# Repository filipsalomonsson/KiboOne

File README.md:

# Kibo One

A keyboard built from the ground up to my personal preferences, using switches and keycaps from 1980s Apple keyboards. Very much a work in progress.

Some design guidelines:

* Must be fun to make
* Alps switches are nice
* AEK-era Apple keycaps are nice
* Stabilizers are the devil
* The width of standard ANSI shift keys is ridiculous
* The width of a standard spacebar is ridiculous
* Actually, no key _really_ deserves to be wider than 2u
* The thumb is underused for modifier keys
* The left-leaning stagger for the left hand on standard keyboards seems a bit silly

More to come.

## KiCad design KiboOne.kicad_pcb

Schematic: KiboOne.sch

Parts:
C1, C2: 22pF; C_0805_2012Metric_Pad1.15x1.40mm_HandSolder
C3, C4: 1uF; C_0805_2012Metric_Pad1.15x1.40mm_HandSolder
D1, D2, D3, D4, D5, D6, D7, D8, D9, D10, D11, D12, D13, D14, D15, D16, D17, D18, D19, D20, D21, D22, D23, D24, D25, D26, D27, D28, D29, D30, D31, D32, D33, D34, D35, D36, D37, D38, D39, D40, D41, D42, D43, D44, D45, D46, D47, D48, D49, D50, D51, D52, D53, D54, D55, D56, D57, D58, D59, D60, D61, D62, D63: LL4148; D_MiniMELF
J1: USB_C_Receptacle; USB_C_Receptacle_Amphenol_12401548E4-2A
R1, R2, R3: 22ohm; R_0805_2012Metric_Pad1.15x1.40mm_HandSolder
SW1: \\; SW_Matias_1.00u
SW2: =; SW_Matias_1.00u
SW3: -; SW_Matias_1.00u
SW4: 0; SW_Matias_1.00u
SW5: 9; SW_Matias_1.00u
SW6: 8; SW_Matias_1.00u
SW7: 7; SW_Matias_1.00u
SW8: 6; SW_Matias_1.00u
SW9: 5; SW_Matias_1.00u
SW10: 4; SW_Matias_1.00u
SW11: 3; SW_Matias_1.00u
SW12: 2; SW_Matias_1.00u
SW13: 1; SW_Matias_1.00u
SW14: esc; SW_Matias_1.00u
SW15: del; SW_Matias_1.50u
SW16: ]; SW_Matias_1.00u
SW17: [; SW_Matias_1.00u
SW18: P; SW_Matias_1.00u
SW19: O; SW_Matias_1.00u
SW20: I; SW_Matias_1.00u
SW21: U; SW_Matias_1.00u
SW22: Y; SW_Matias_1.00u
SW23: T; SW_Matias_1.00u
SW24: R; SW_Matias_1.00u
SW25: E; SW_Matias_1.00u
SW26: W; SW_Matias_1.00u
SW27: Q; SW_Matias_1.00u
SW28: ⇥; SW_Matias_1.50u
SW29: return; SW_Matias_2.00u
SW30: '; SW_Matias_1.00u
SW31: ;; SW_Matias_1.00u
SW32: L; SW_Matias_1.00u
SW33: K; SW_Matias_1.00u
SW34: J; SW_Matias_1.00u
SW35: H; SW_Matias_1.00u
SW36: G; SW_Matias_1.00u
SW37: F; SW_Matias_1.00u
SW38: D; SW_Matias_1.00u
SW39: S; SW_Matias_1.00u
SW40: A; SW_Matias_1.00u
SW41: cmd1; SW_Matias_1.50u
SW42: /; SW_Matias_1.00u
SW43: ↑; SW_Matias_1.00u
SW44: .; SW_Matias_1.00u
SW45: ,; SW_Matias_1.00u
SW46: M; SW_Matias_1.00u
SW47: N; SW_Matias_1.00u
SW48: B; SW_Matias_1.00u
SW49: V; SW_Matias_1.00u
SW50: C; SW_Matias_1.00u
SW51: X; SW_Matias_1.00u
SW52: Z; SW_Matias_1.00u
SW53: tilde; SW_Matias_1.00u
SW54: shift; SW_Matias_1.50u
SW55: →; SW_Matias_1.00u
SW56: ↓; SW_Matias_1.00u
SW57: ←; SW_Matias_1.00u
SW58: cmd3; SW_Matias_1.50u
SW59: space; SW_Matias_2.25u
SW60: Fn; SW_Matias_1.00u
SW61: cmd2; SW_Matias_1.75u
SW62: ⌥; SW_Matias_1.25u
SW63: ctrl; SW_Matias_1.50u
SW_RESET1: RESET; SW_SPST_EVPBF
U1: ATmega32U4-AU; TQFP-44_10x10mm_P0.8mm
Y1: 16 MHz; Crystal_SMD_3225-4Pin_3.2x2.5mm_HandSoldering

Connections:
/D1+: J1.A6, J1.B6, R2.2
/D1-: J1.A7, J1.B7, R1.2
Col1: D8.1, D9.1, D22.1, D23.1, D35.1, D36.1, D48.1, D49.1, U1.18 (PD0)
Col2: D7.1, D10.1, D21.1, D24.1, D34.1, D37.1, D47.1, D50.1, U1.28 (PB4)
Col3: D6.1, D11.1, D20.1, D25.1, D33.1, D38.1, D46.1, D51.1, U1.19 (PD1)
Col4: D5.1, D12.1, D19.1, D26.1, D32.1, D39.1, D45.1, D52.1, U1.27 (PD7)
Col5: D4.1, D13.1, D18.1, D27.1, D31.1, D40.1, D44.1, D53.1, U1.20 (PD2)
Col6: D3.1, D14.1, D17.1, D28.1, D30.1, D41.1, D54.1, D58.1, U1.26 (PD6)
Col7: D2.1, D16.1, D29.1, D59.1, D60.1, D61.1, D62.1, D63.1, U1.21 (PD3)
Col8: D1.1, D15.1, D42.1, D43.1, D55.1, D56.1, D57.1, U1.25 (PD4)
D+: R2.1, U1.4 (D+)
D-: R1.1, U1.3 (D-)
GND: C1.2, C2.2, C3.1, C4.2, J1.A1, J1.A12, J1.B1, J1.B12, J1.S1, SW_RESET1.2, U1.5 (UGND), U1.15 (GND), U1.23 (GND), U1.35 (GND), U1.43 (GND)
unnamed: C1.1, U1.17 (XTAL1), Y1.1
unnamed: C2.1, U1.16 (XTAL2), Y1.2
unnamed: C4.1, U1.6 (UCAP)
unnamed: D1.2, SW1.2
unnamed: D2.2, SW2.2
unnamed: D3.2, SW3.2
unnamed: D4.2, SW4.2
unnamed: D5.2, SW5.2
unnamed: D6.2, SW6.2
unnamed: D7.2, SW7.2
unnamed: D8.2, SW8.2
unnamed: D9.2, SW9.2
unnamed: D10.2, SW10.2
unnamed: D11.2, SW11.2
unnamed: D12.2, SW12.2
unnamed: D13.2, SW13.2
unnamed: D14.2, SW14.2
unnamed: D15.2, SW15.2
unnamed: D16.2, SW16.2
unnamed: D17.2, SW17.2
unnamed: D18.2, SW18.2
unnamed: D19.2, SW19.2
unnamed: D20.2, SW20.2
unnamed: D21.2, SW21.2
unnamed: D22.2, SW22.2
unnamed: D23.2, SW23.2
unnamed: D24.2, SW24.2
unnamed: D25.2, SW25.2
unnamed: D26.2, SW26.2
unnamed: D27.2, SW27.2
unnamed: D28.2, SW28.2
unnamed: D29.2, SW29.2
unnamed: D30.2, SW30.2
unnamed: D31.2, SW31.2
unnamed: D32.2, SW32.2
unnamed: D33.2, SW33.2
unnamed: D34.2, SW34.2
unnamed: D35.2, SW35.2
unnamed: D36.2, SW36.2
unnamed: D37.2, SW37.2
unnamed: D38.2, SW38.2
unnamed: D39.2, SW39.2
unnamed: D40.2, SW40.2
unnamed: D41.2, SW41.2
unnamed: D42.2, SW42.2
unnamed: D43.2, SW43.2
unnamed: D44.2, SW44.2
unnamed: D45.2, SW45.2
unnamed: D46.2, SW46.2
unnamed: D47.2, SW47.2
unnamed: D48.2, SW48.2
unnamed: D49.2, SW49.2
unnamed: D50.2, SW50.2
unnamed: D51.2, SW51.2
unnamed: D52.2, SW52.2
unnamed: D53.2, SW53.2
unnamed: D54.2, SW54.2
unnamed: D55.2, SW55.2
unnamed: D56.2, SW56.2
unnamed: D57.2, SW57.2
unnamed: D58.2, SW58.2
unnamed: D59.2, SW59.2
unnamed: D60.2, SW60.2
unnamed: D61.2, SW61.2
unnamed: D62.2, SW62.2
unnamed: D63.2, SW63.2
RESET: R3.2, SW_RESET1.1, U1.13 (~RESET)
Row1: SW43.1, SW49.1, SW50.1, SW51.1, SW52.1, SW53.1, SW54.1, SW60.1, U1.11 (PB3)
Row2: SW36.1, SW37.1, SW38.1, SW39.1, SW40.1, SW41.1, SW57.1, SW61.1, U1.10 (PB2)
Row3: SW23.1, SW24.1, SW25.1, SW26.1, SW27.1, SW28.1, SW56.1, SW62.1, U1.9 (PB1)
Row4: SW9.1, SW10.1, SW11.1, SW12.1, SW13.1, SW14.1, SW55.1, SW63.1, U1.8 (PB0)
Row5: SW1.1, SW2.1, SW3.1, SW4.1, SW5.1, SW6.1, SW7.1, SW8.1, U1.41 (PF0)
Row6: SW15.1, SW16.1, SW17.1, SW18.1, SW19.1, SW20.1, SW21.1, SW22.1, U1.40 (PF1)
Row7: SW29.1, SW30.1, SW31.1, SW32.1, SW33.1, SW34.1, SW35.1, SW42.1, U1.39 (PF4)
Row8: SW44.1, SW45.1, SW46.1, SW47.1, SW48.1, SW58.1, SW59.1, U1.38 (PF5)

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
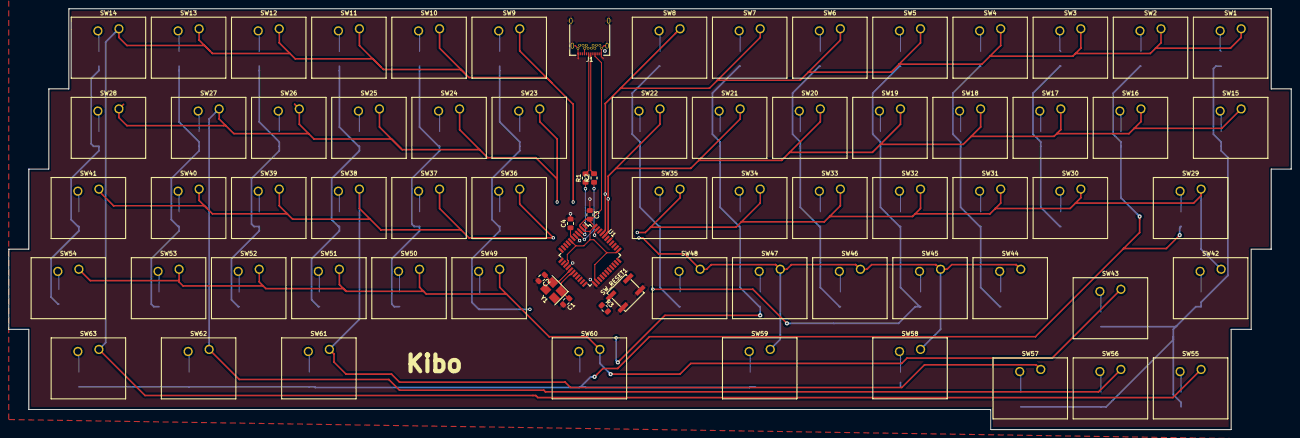
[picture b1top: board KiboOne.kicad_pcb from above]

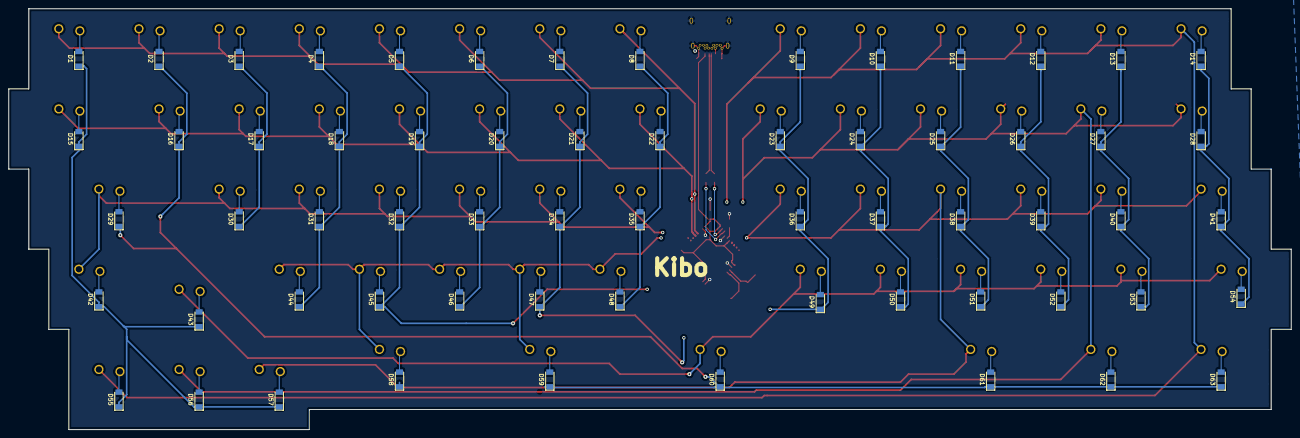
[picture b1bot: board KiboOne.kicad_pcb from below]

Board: 2 copper layers, 304.8 x 100.0 mm, 137 parts (63 on the bottom side), 89 nets.

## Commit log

2018-09-01 First pass at schema and footprint layout
2018-09-01 Basic routing, some logo work
2018-09-01 Work work work
2018-09-02 Various faffing about
2018-09-15 Add a brief readne
2018-09-15 Prep for dual-board design
2019-01-08 Typo in README.md
